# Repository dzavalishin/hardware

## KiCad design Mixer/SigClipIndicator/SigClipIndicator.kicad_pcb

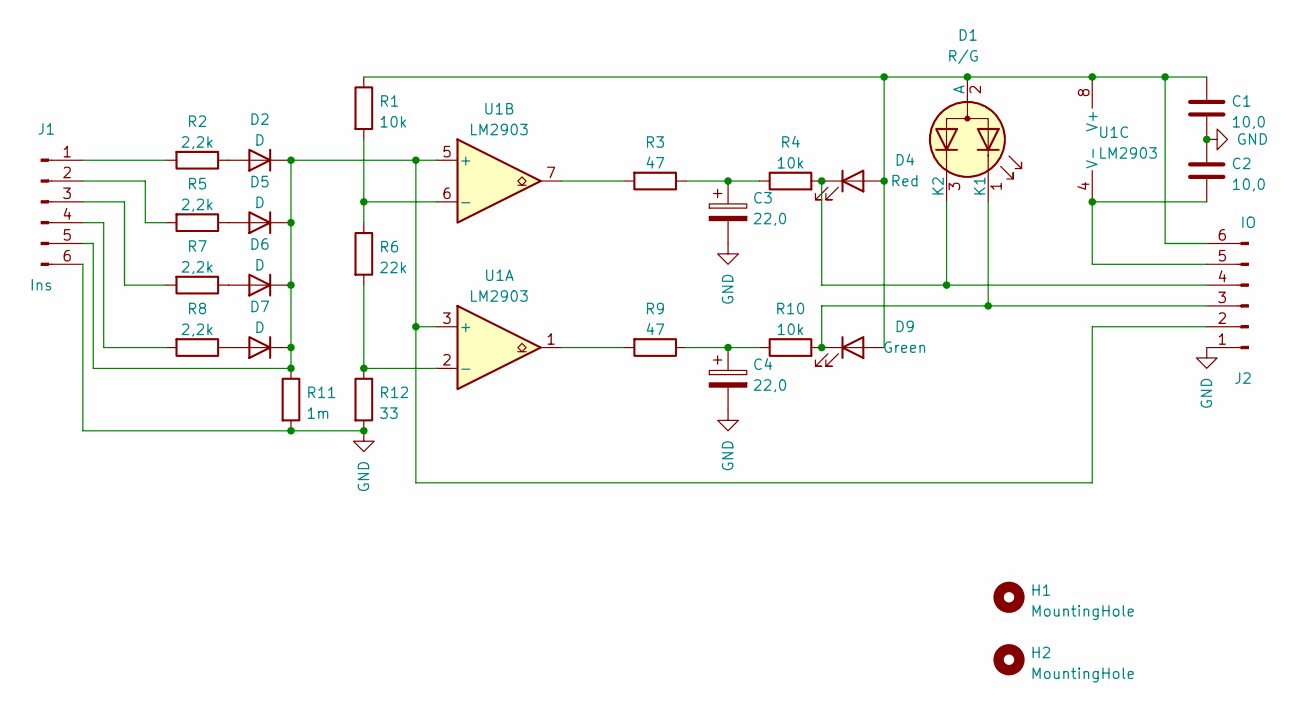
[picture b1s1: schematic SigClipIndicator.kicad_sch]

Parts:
C1, C2: 10,0; C_0805_2012Metric_Pad1.18x1.45mm_HandSolder
C3, C4: 22,0; C_0805_2012Metric_Pad1.18x1.45mm_HandSolder
D1: R/G; LED_D3.0mm-3
D2, D5, D6, D7: D; D_MiniMELF_Handsoldering
D4: Red; LED_D3.0mm
D9: Green; LED_D3.0mm
H1, H2: MountingHole; MountingHole_2.2mm_M2
J1: Ins; PinHeader_1x06_P2.54mm_Vertical
J2: IO; PinHeader_1x06_P2.54mm_Vertical
R1, R4, R10: 10k; R_1206_3216Metric_Pad1.30x1.75mm_HandSolder
R2, R5, R7, R8: 2,2k; R_1206_3216Metric_Pad1.30x1.75mm_HandSolder
R3, R9: 47; R_1206_3216Metric_Pad1.30x1.75mm_HandSolder
R6: 22k; R_1206_3216Metric_Pad1.30x1.75mm_HandSolder
R11: 1m; R_1206_3216Metric_Pad1.30x1.75mm_HandSolder
R12: 33; R_1206_3216Metric_Pad1.30x1.75mm_HandSolder
U1: LM2903; SOIC-8_3.9x4.9mm_P1.27mm

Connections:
GND: C1.1, C2.2, C3.2, C4.2, J1.6, J2.1, R11.2, R12.2
unnamed: C1.2, D1.2 (A), D4.2 (A), D9.2 (A), J2.6, R1.1, U1.8 (V+)
unnamed: C2.1, J2.5, U1.4 (V-)
unnamed: C3.1, R3.1, R4.1
unnamed: C4.1, R9.1, R10.1
unnamed: D1.1 (K1), D9.1 (K), J2.3, R10.2
unnamed: D1.3 (K2), D4.1 (K), J2.4, R4.2
unnamed: D2.1 (K), D5.1 (K), D6.1 (K), D7.1 (K), J1.5, J2.2, R11.1, U1.3 (+), U1.5 (+)
unnamed: D2.2 (A), R2.1
unnamed: D5.2 (A), R5.1
unnamed: D6.2 (A), R7.1
unnamed: D7.2 (A), R8.1
unnamed: J1.1, R2.2
unnamed: J1.2, R5.2
unnamed: J1.3, R7.2
unnamed: J1.4, R8.2
unnamed: R1.2, R6.1, U1.6 (-)
unnamed: R3.2, U1.7
unnamed: R9.2, U1.1
unnamed: R6.2, R12.1, U1.2 (-)

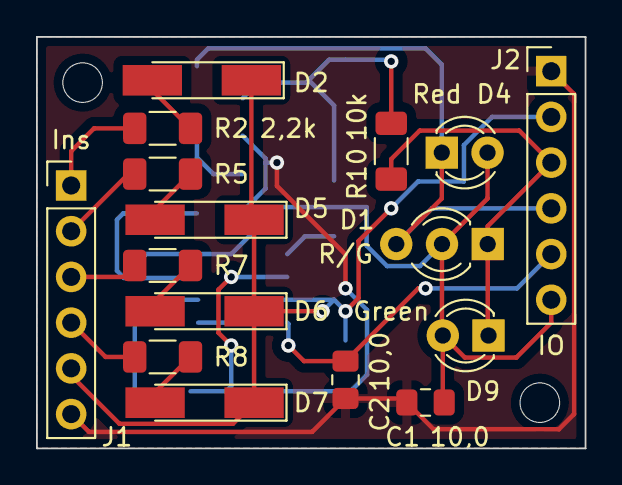
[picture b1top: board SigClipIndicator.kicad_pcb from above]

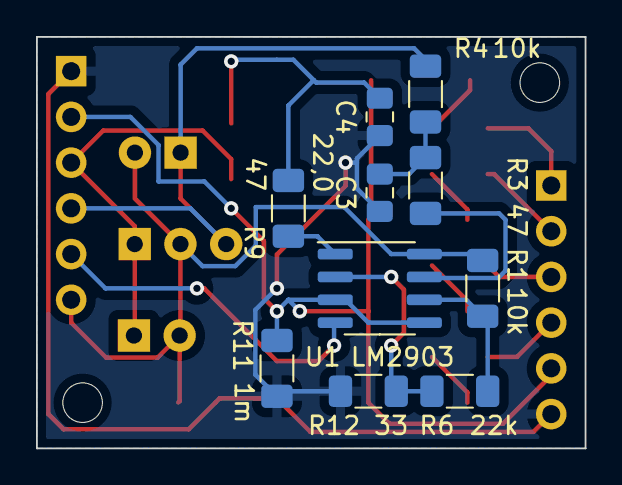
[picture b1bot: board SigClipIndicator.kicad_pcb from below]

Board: 2 copper layers, 30.5 x 22.9 mm, 28 parts (10 on the bottom side), 20 nets.

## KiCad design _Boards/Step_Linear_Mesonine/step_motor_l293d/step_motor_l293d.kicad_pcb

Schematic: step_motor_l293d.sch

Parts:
C1, C3, C5: 0,1; C_1206_HandSoldering
C4, C8: 47,0; CP_Elec_6.3x5.3
C6, C7: 1,0; C_0805_HandSoldering
C9, C10: 0,33; C_0805_HandSoldering
C11: 100,0; CP_Elec_6.3x5.7
D1: A; LED_1206_HandSoldering
D2: B; LED_1206_HandSoldering
D3: Over; LED_1206_HandSoldering
D4: D; LED_1206_HandSoldering
D5: C; LED_1206_HandSoldering
J1: Motor; Pin_Header_Straight_1x04_Pitch2.54mm
J2: +12; TerminalBlock_bornier-2_P5.08mm
J3: In; Pin_Header_Straight_1x06_Pitch2.54mm
J4: Pwr; Pin_Header_Straight_1x06_Pitch2.54mm
Q1: MMBT3904; SOT-23
R1: 0,2 2W 1%; R_2512_HandSoldering
R2: 200 1%; R_1206_HandSoldering
R3: 1,5m; R_1206_HandSoldering
R4, R5, R7, R10, R11, R12: 10k; R_1206_HandSoldering
R6: 9,1k; R_1206_HandSoldering
R8, R9, R14, R15, R16: 560; R_1206_HandSoldering
R13: 2k 1%; R_1206_HandSoldering
RV1: 1m; Potentiometer_Trimmer_Bourns_3296W
RV2: 1k; Potentiometer_Triwood_RM-065
U1: TL082; DIP-8_W7.62mm
U2: L293D; DIP-16_W7.62mm
U3: L78L05; TO-92_Inline_Narrow_Oval

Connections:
+5V: C3.1, C10.1, C11.1, J4.2, U2.16, U3.1
+12V: C1.1, C8.1, C9.1, J4.1, R1.1, R2.1, R6.2, U1.8, U3.3; also elsewhere on the board
/Buck/Power_In: J2.2; also elsewhere on the board
/MA: J3.1, U2.2
/MB: J3.3, U2.7
/MC: J3.4, U2.10
/MD: J3.2, U2.15
/MPower: C4.1, C5.1, R1.2, R4.1, U2.8
/Overload: J4.4, R3.1, R14.2, U1.7
/Run: J3.5, U2.1, U2.9
/Sense: C6.1, J4.3, Q1.2, R7.2, R13.1
GND: C1.2, C3.2, C4.2, C5.2, C6.2, C7.2, C8.2, C9.2, C10.2, C11.2, D1.1, D2.1, D3.1, D4.1, D5.1, J2.1, J3.6, J4.6, R11.2, R12.2, R13.2, RV2.3, U1.4, U2.4, U2.5, U2.12, U2.13, U3.2; also elsewhere on the board
unnamed: C7.1, R10.2, RV2.2
unnamed: D1.2, R8.1
unnamed: D2.2, R9.1
unnamed: D3.2, R14.1
unnamed: D4.2, R15.2
unnamed: D5.2, R16.2
unnamed: J1.1, R15.1, U2.14
unnamed: J1.2, R16.1, U2.11
unnamed: J1.3, R9.2, U2.6
unnamed: J1.4, R8.2, U2.3
unnamed: Q1.1, U1.1
unnamed: Q1.3, R2.2, R5.1
unnamed: R3.2, RV1.3
unnamed: R6.1, RV2.1
unnamed: R7.1, RV1.1, RV1.2, U1.5
unnamed: R10.1, U1.6
unnamed: R4.2, R11.1, U1.2
unnamed: R5.2, R12.1, U1.3

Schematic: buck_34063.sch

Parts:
C2, C12, C14: 0,1; C_1206_HandSoldering
C13, C16: 100,0; CP_Elec_6.3x5.7
C15: 220,0; CP_Elec_6.3x5.7
C17: 390; C_1206_HandSoldering
D6, D7: SS34; D_SMB-SMC_Universal_Handsoldering
L1: 100uH; Inductor_Taiyo-Yuden_NR-40xx_HandSoldering
L2: 47uH; Inductor_Taiyo-Yuden_NR-40xx_HandSoldering
R17: 1,5 1W; R_2512_HandSoldering
R18: 11k; R_1206_HandSoldering
R19: 1,3k; R_1206_HandSoldering
U4: MC34063; SOIC-8_3.9x4.9mm_Pitch1.27mm

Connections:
+12V: C16.1, L2.2, R18.2; also elsewhere on the board
/Buck/Power_In: C12.2, D6.2; also elsewhere on the board
GND: C2.1, C12.1, C13.2, C14.2, C15.2, C16.2, C17.2, D7.2, R19.2, U4.4; also elsewhere on the board
unnamed: C2.2, R17.2, U4.1, U4.7, U4.8
unnamed: C13.1, D6.1, R17.1, U4.6
unnamed: C14.1, C15.1, L1.2, L2.1
unnamed: C17.1, U4.3
unnamed: D7.1, L1.1, U4.2
unnamed: R18.1, R19.1, U4.5

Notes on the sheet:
12v out, 1.25v sense level

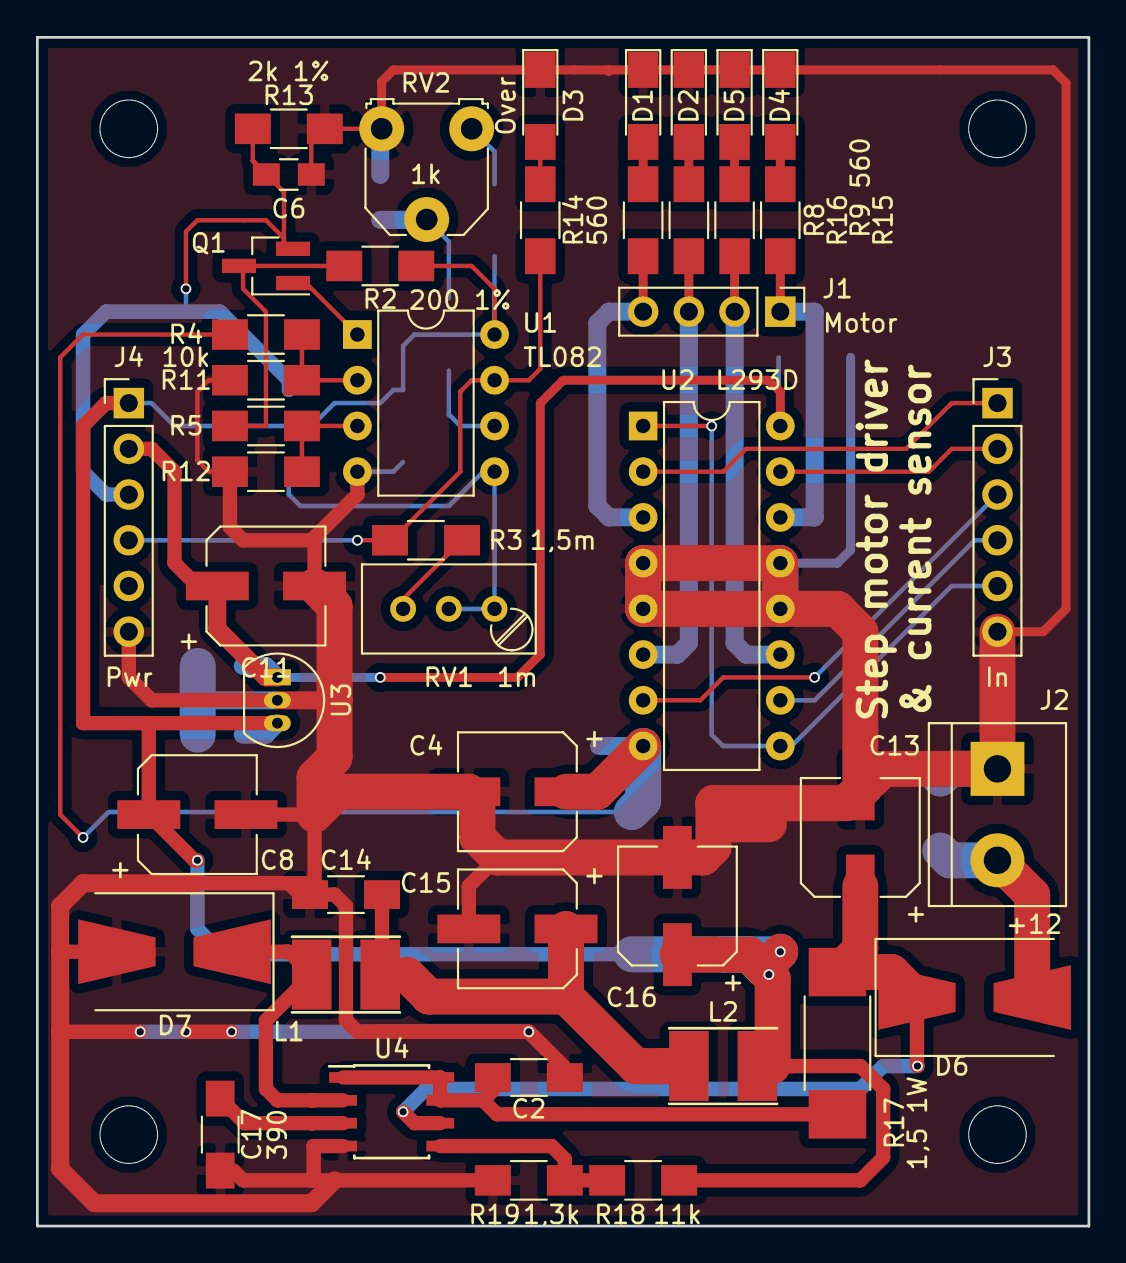
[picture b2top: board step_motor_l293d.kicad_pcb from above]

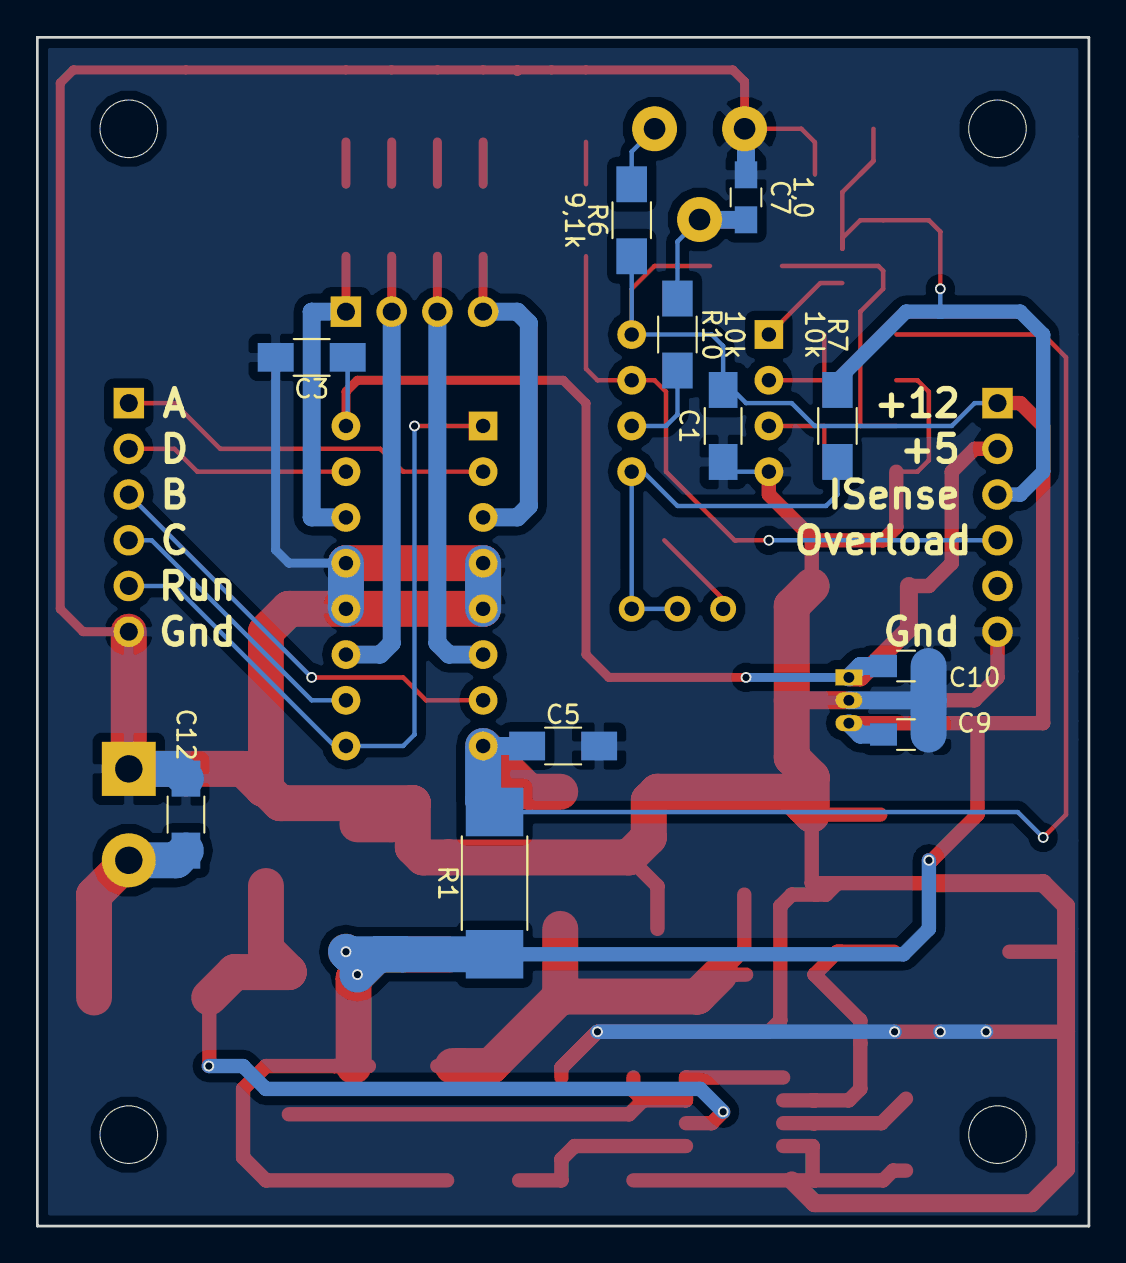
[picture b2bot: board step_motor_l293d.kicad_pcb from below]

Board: 2 copper layers, 58.4 x 66.0 mm, 60 parts (11 on the bottom side), 36 nets.

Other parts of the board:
Hole: MountingHole_3.2mm_M3
Hole#2, Hole#3, Hole#4: MountingHole_3.2mm_M3

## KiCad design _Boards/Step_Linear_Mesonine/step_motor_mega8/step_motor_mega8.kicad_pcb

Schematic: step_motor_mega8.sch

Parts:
C1, C2, C3: 0,1; C_1206_HandSoldering
C4, C5: 18; C_1206_HandSoldering
D1: Err; LED_1206_HandSoldering
D2: Tx; LED_1206_HandSoldering
D3: Run; LED_1206_HandSoldering
D4: 5v6; D_1206
J1: ISP; Socket_Strip_Straight_2x05_Pitch2.54mm
J3: In; Pin_Header_Straight_1x06_Pitch2.54mm
J4: Pwr; Pin_Header_Straight_1x06_Pitch2.54mm
J5: RS485; TerminalBlock_bornier-2_P5.08mm
J6: Open/~Close; TerminalBlock_bornier-2_P5.08mm
R1: 10k; R_1206_HandSoldering
R2, R3: 47; R_1206_HandSoldering
R4, R5, R6, R8: 560; R_1206_HandSoldering
R7, R9: 1k; R_1206_HandSoldering
U1: ATMEGA8-16PU; DIP-28_W7.62mm
U2: MAX485E; SOIC-8_3.9x4.9mm_Pitch1.27mm
U3: PC817; SOP-4_4.4x2.8mm_Pitch1.27mm
Y1: 8MHz; Crystal_HC49-4H_Vertical

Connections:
+5V: C1.2, C3.2, J4.2, R1.1, R9.1, U1.7, U1.20, U2.8 (VCC); also elsewhere on the board
/Di0: R9.2, U1.14, U3.4
/MA: J3.1, U1.27
/MB: J3.3, U1.25
/MC: J3.4, U1.24
/MD: J3.2, U1.26
/Overload: J4.4, U1.11
/Run: J3.5, R6.2, U1.23
/S1: U1.4; also elsewhere on the board
/S2: U1.5; also elsewhere on the board
GND: C1.1, C2.1, C3.1, C4.1, C5.1, D1.1, D2.1, D3.1, J1.4, J1.6, J1.8, J1.10, J3.6, J4.6, U1.8, U1.22, U2.5 (GND), U3.3; also elsewhere on the board
unnamed: C2.2, J1.5, R1.2, U1.1
unnamed: C4.2, U1.9, Y1.1
unnamed: C5.2, U1.10, Y1.2
unnamed: D1.2, R4.1
unnamed: D2.2, R5.1
unnamed: D3.2, R6.1
unnamed: D4.1, R7.1, R8.1
unnamed: D4.2, J6.1, U3.2
unnamed: J1.1, U1.17
unnamed: J1.7, U1.19
unnamed: J1.9, U1.18
unnamed: J5.1, R2.1
unnamed: J5.2, R3.1
unnamed: J6.2, R7.2
unnamed: R2.2, U2.7 (B)
unnamed: R3.2, U2.6 (A)
unnamed: R4.2, U1.28
unnamed: R5.2, U1.6, U2.2 (~RE), U2.3 (DE)
unnamed: R8.2, U3.1
unnamed: U1.2, U2.1 (RO)
unnamed: U1.3, U2.4 (DI)

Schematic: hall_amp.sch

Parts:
C10: 0,1; C_1206_HandSoldering
C11: 1,0; C_0805_HandSoldering
D6: S1; LED_1206_HandSoldering
D7: S2; LED_1206_HandSoldering
J2: Hall; Pin_Header_Angled_2x03_Pitch2.54mm
R13, R20, R22, R23, R27, R28: 1k; R_1206_HandSoldering
R21, R26: 220k; R_1206_HandSoldering
R24, R25: 560; R_1206_HandSoldering
RV3: 1k; Potentiometer_Triwood_RM-065
U6: LM2904; SOIC-8_3.9x4.9mm_Pitch1.27mm

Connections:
+5V: C10.1, J2.5, J2.6, R13.2, U6.8; also elsewhere on the board
/S1: R21.1, R24.2, U6.1; also elsewhere on the board
/S2: R25.2, R26.1, U6.7; also elsewhere on the board
GND: C10.2, C11.2, D6.1, D7.1, J2.3, J2.4, R20.1, U6.4; also elsewhere on the board
unnamed: C11.1, R23.2, R28.2, RV3.2
unnamed: D6.2, R24.1
unnamed: D7.2, R25.1
unnamed: J2.1, R22.2
unnamed: J2.2, R27.2
unnamed: R13.1, RV3.1
unnamed: R20.2, RV3.3
unnamed: R21.2, R22.1, U6.3
unnamed: R23.1, U6.2
unnamed: R26.2, R27.1, U6.5
unnamed: R28.1, U6.6

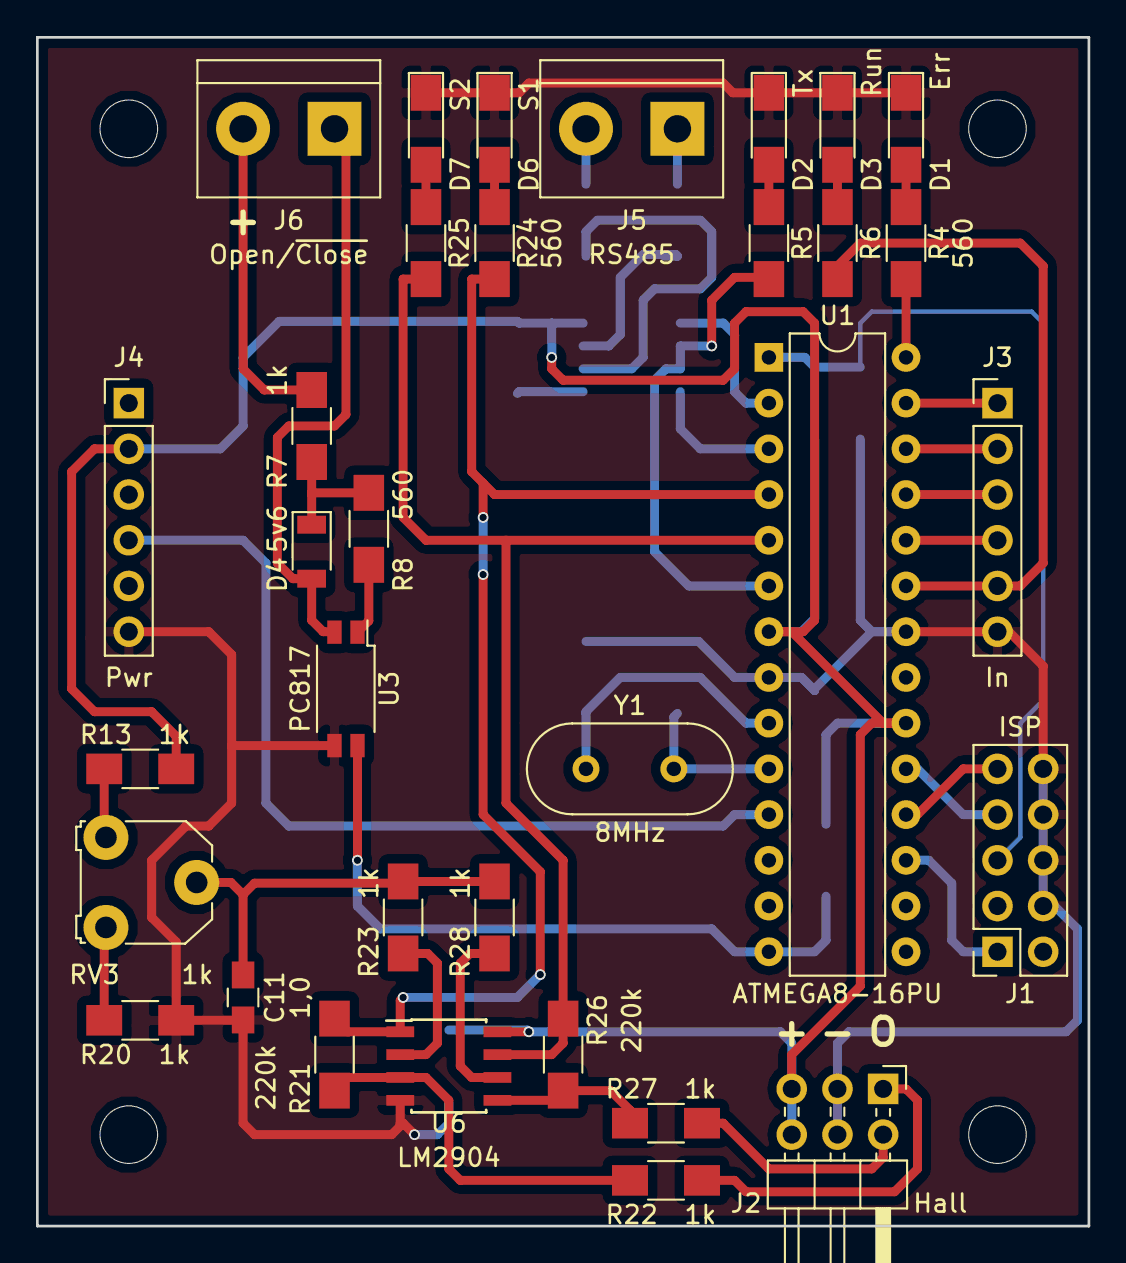
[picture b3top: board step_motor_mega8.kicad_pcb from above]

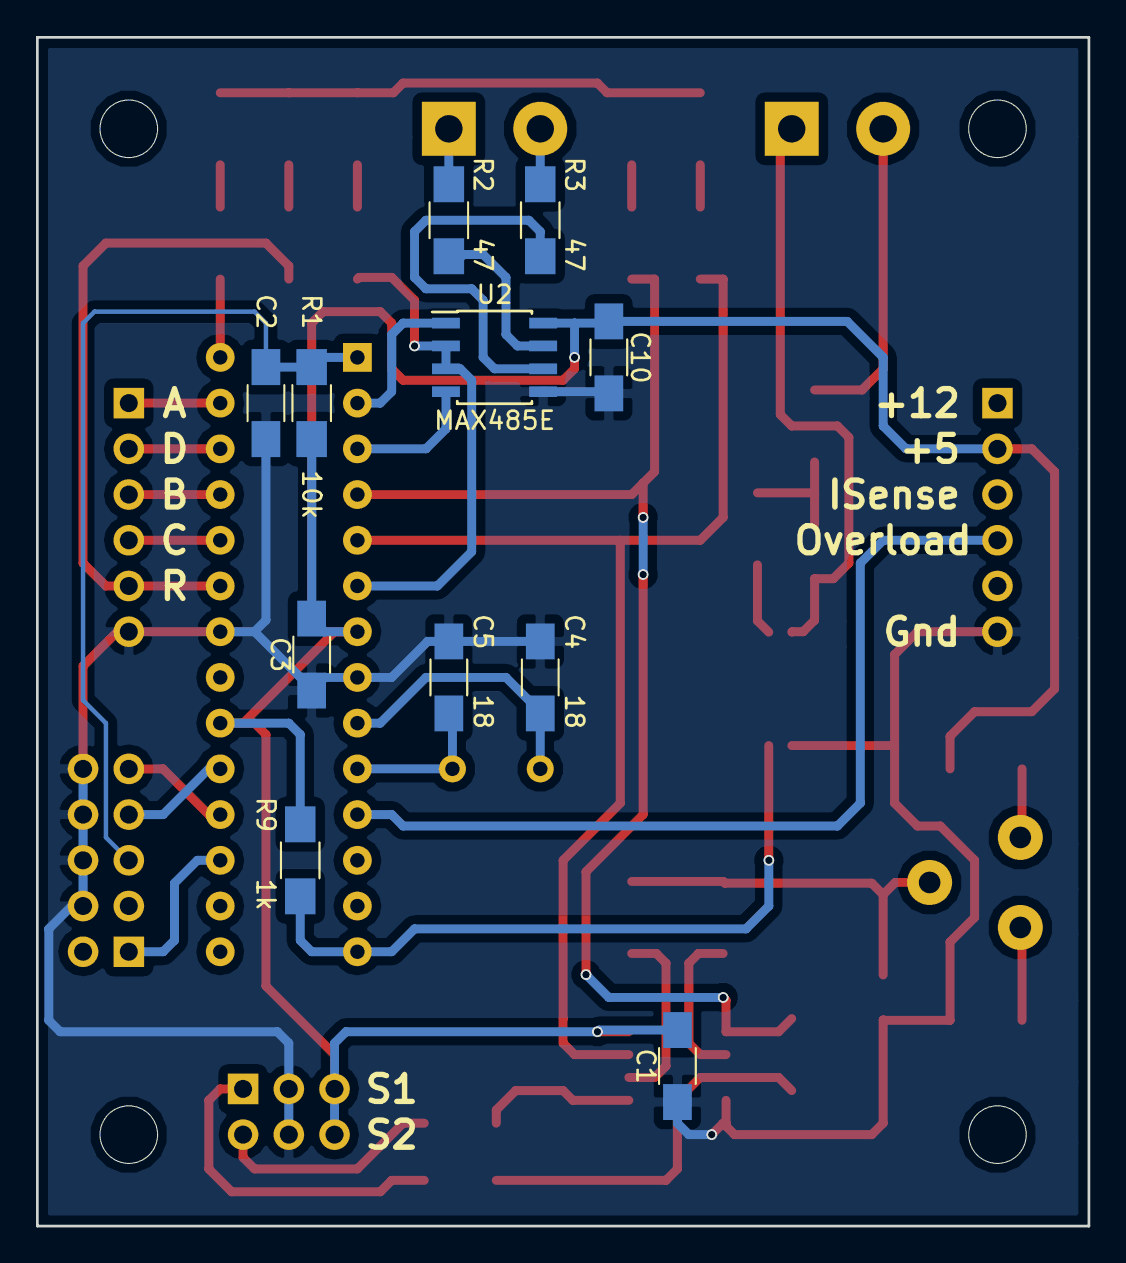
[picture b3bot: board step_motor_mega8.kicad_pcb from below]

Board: 2 copper layers, 58.4 x 66.0 mm, 48 parts (11 on the bottom side), 43 nets.

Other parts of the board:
Hole: MountingHole_3.2mm_M3
Hole#2, Hole#3, Hole#4: MountingHole_3.2mm_M3

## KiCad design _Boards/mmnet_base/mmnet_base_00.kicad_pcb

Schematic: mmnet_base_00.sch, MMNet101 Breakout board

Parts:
C1, C2, C4, C6: 0,1; C_1206_HandSoldering
C3: 100,0; SMD-2512_Pol
C5: 10,0; SMD-2512_Pol
D1: D; D_MELF_Handsoldering
D2: Pwr; LED_D3.0mm
D3: Tx0; LED_D3.0mm
D4: Tx1; LED_D3.0mm
D5: Fail; LED_D3.0mm
D6: IO; LED_D3.0mm
F1: 0,1A; SMD-1206_Pol
J1: 24V; TerminalBlock_Pheonix_MPT-2.54mm_2pol
J2: RS485; TerminalBlock_Pheonix_MPT-2.54mm_2pol
J3: Ext_IO_0; TerminalBlock_Pheonix_MPT-2.54mm_3pol
J4: Ext_IO_1; TerminalBlock_Pheonix_MPT-2.54mm_5pol
J5: Ai0-1; TerminalBlock_Pheonix_MPT-2.54mm_3pol
J6: Ai2-3; TerminalBlock_Pheonix_MPT-2.54mm_3pol
J7: 1Wire; TerminalBlock_Pheonix_MPT-2.54mm_6pol
P1: VR+In; Socket_Strip_Straight_1x01
P2: VR-In; Socket_Strip_Straight_1x01
P3: Bus; Socket_Strip_Straight_2x05
P4: VR+Out; Socket_Strip_Straight_1x01
P5: VR-Out; Socket_Strip_Straight_1x01
P6: MMNet_L; Socket_Strip_Straight_1x20
P7: MMNet_R; Socket_Strip_Straight_1x20
P10: Extension; Socket_Strip_Straight_2x08
P11: JTAG/AnalogExt; Socket_Strip_Straight_2x05
R1, R2, R3, R4, R5, R6, R11: 4,7k; R_1206_HandSoldering
R7, R8, R9, R10, R12: 5,6k; R_1206_HandSoldering
R13, R14: 3k 1%; R_Axial_DIN0207_L6.3mm_D2.5mm_P10.16mm_Horizontal
R15, R16: 27k 1%; R_Axial_DIN0204_L3.6mm_D1.6mm_P2.54mm_Vertical
R17, R18, R19, R20: 100; R_1206_HandSoldering
R21, R22, R23, R24: 10k; R_1206_HandSoldering
U1: SP3485CN; SOIC-8_3.9x4.9mm_Pitch1.27mm
U2: DS2401; TO-92_Rugged
U3: DS18B20; TO-92_Rugged

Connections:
+5V: C1.1, C2.1, C3.1, D5.2, D6.2, F1.2, P3.6, P4.1, P6.19, P10.8, P11.4, R1.2, R2.2, R3.2, R4.2, R5.2, R6.2, R7.2, R11.1, R21.2, R22.2, R23.2, R24.2, U1.8 (VCC), U3.3 (VDD)
/1Wire: P7.18, R11.2, U2.2 (DQ), U3.2 (DQ)
/1Wire_B0: P6.13, R3.1, R17.2
/1Wire_B1: P6.14, R4.1, R18.2
/1Wire_B2: P6.15, R5.1, R19.2
/1Wire_B3: P6.16, R6.1, R20.2
/ADC0: J5.3, P7.10
/ADC1: J5.1, P7.11
/ADC2: P7.12, R13.1, R15.2
/ADC3: P7.13, R14.1, R16.2
/ADC4/TCK: P7.14, P11.1, R21.1
/ADC5/TMS: P7.15, P11.5, R22.1
/ADC6/TDO: P7.16, P11.3, R23.1
/ADC7/TDI: P7.17, P11.9, R24.1
/ARef: C4.2, P7.9
/I2C_SCL: P3.8, P6.9, P10.5, R1.1
/I2C_SDA: P3.4, P6.10, P10.7, R2.1
/LED_Fail: P7.4, R10.2
/LED_Io: P7.19, R12.2
/RxD0: P7.8, P10.16
/RxD1: P6.11, U1.1 (RO)
/SPI_MISO: P3.7, P6.4
/SPI_MOSI: P3.5, P6.3
/SPI_SCK: P3.3, P6.2
/TxD0: P7.7, P10.14
/TxD1: P6.12, U1.4 (DI)
/TxE0: P6.7, R8.2
/TxE1: P6.8, R9.2, U1.2 (~RE~), U1.3 (DE)
/~Reset: P7.20, P11.6
/~SS0: P3.1, P6.1
/~SS1: P3.9, P6.5
GND: C1.2, C2.2, C3.2, C4.1, C5.2, C6.1, D2.1, D3.1, D4.1, J1.2, J3.2, J4.1, J5.2, J6.2, J7.6, P2.1, P3.2, P3.10, P5.1, P6.20, P10.6, P11.2, P11.10, R13.2, R14.2, U1.5 (GND), U2.1 (GND), U3.1 (GND)
unnamed: C5.1, C6.2, F1.1, J7.1
unnamed: D1.1, P1.1
unnamed: D1.2, J1.1
unnamed: D2.2, R7.1
unnamed: D3.2, R8.1
unnamed: D4.2, R9.1
unnamed: D5.1, R10.1
unnamed: D6.1, R12.1
unnamed: J2.1, U1.6 (A)
unnamed: J2.2, U1.7 (B)
unnamed: J3.1, P10.3
unnamed: J3.3, P10.1
unnamed: J4.2, P10.15
unnamed: J4.3, P10.13
unnamed: J4.4, P10.11
unnamed: J4.5, P10.9
unnamed: J6.1, R16.1
unnamed: J6.3, R15.1
unnamed: J7.2, R17.1
unnamed: J7.3, R18.1
unnamed: J7.4, R19.1
unnamed: J7.5, R20.1
unnamed: P7.1, P10.2
unnamed: P7.2, P10.4
unnamed: P7.5, P10.10
unnamed: P7.6, P10.12

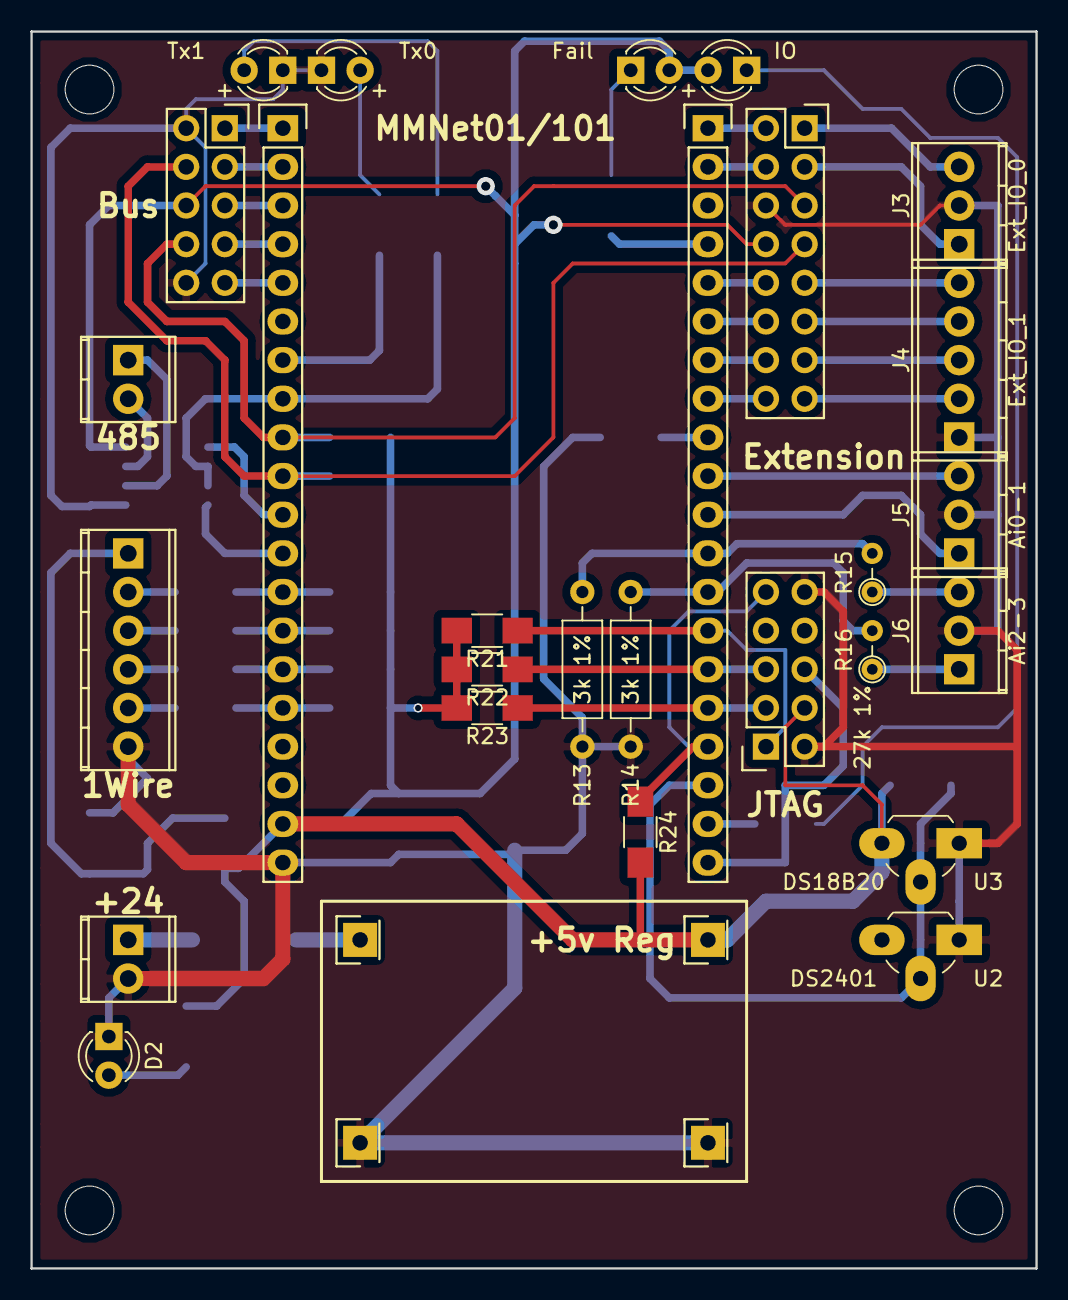
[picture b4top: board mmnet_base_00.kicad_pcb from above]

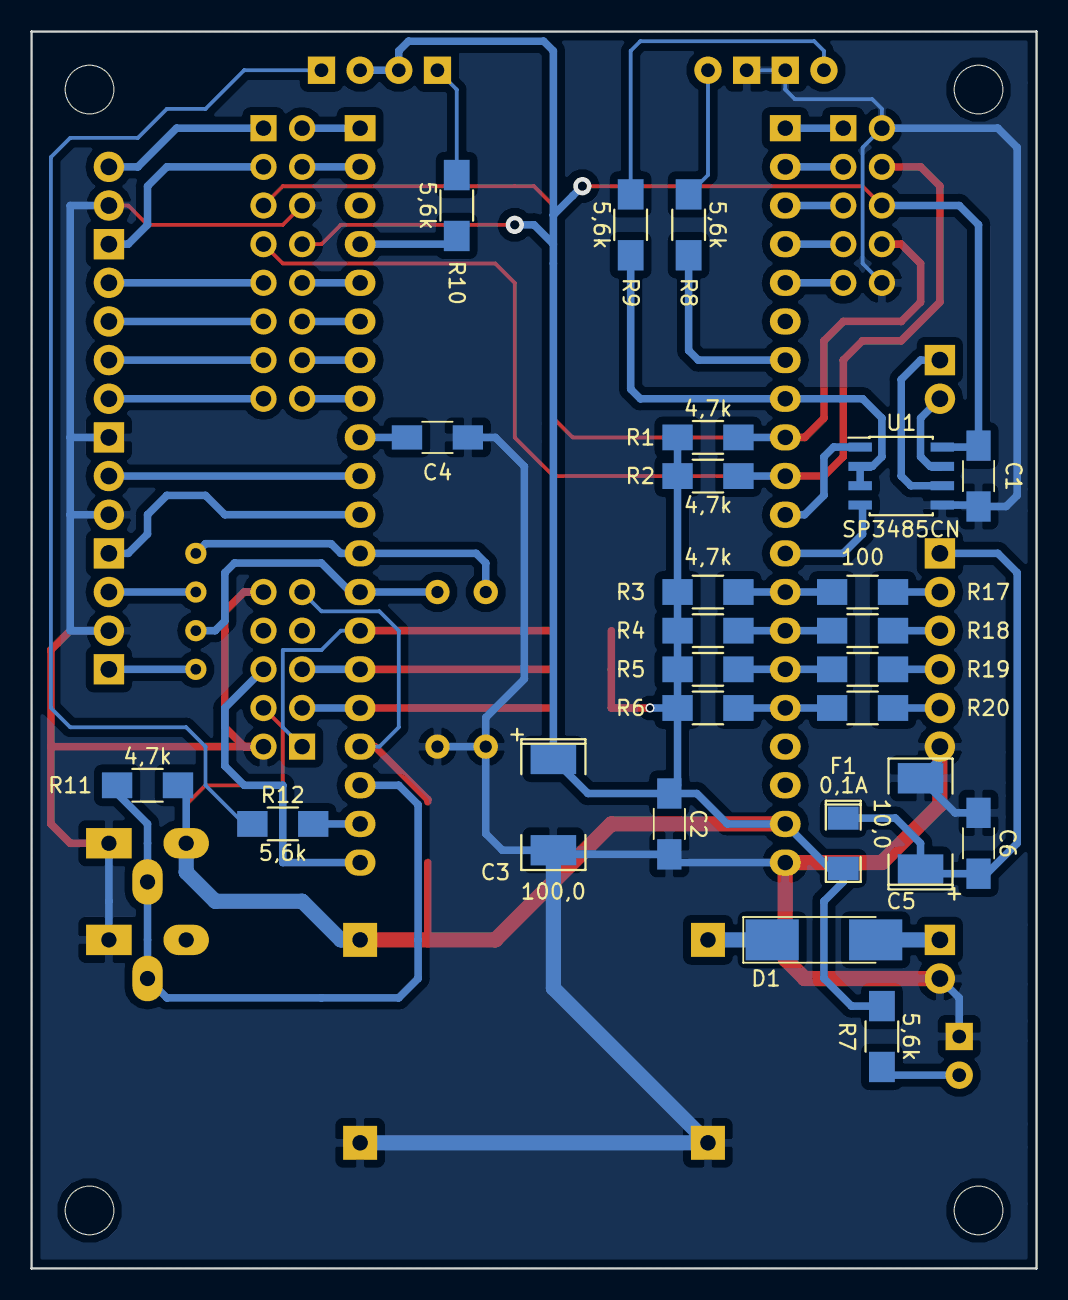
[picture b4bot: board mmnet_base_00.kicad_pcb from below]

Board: 2 copper layers, 66.0 x 81.3 mm, 60 parts (25 on the bottom side), 58 nets.

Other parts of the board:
hole: MountingHole_3.2mm_M3
hole#2, hole#3, hole#4: MountingHole_3.2mm_M3

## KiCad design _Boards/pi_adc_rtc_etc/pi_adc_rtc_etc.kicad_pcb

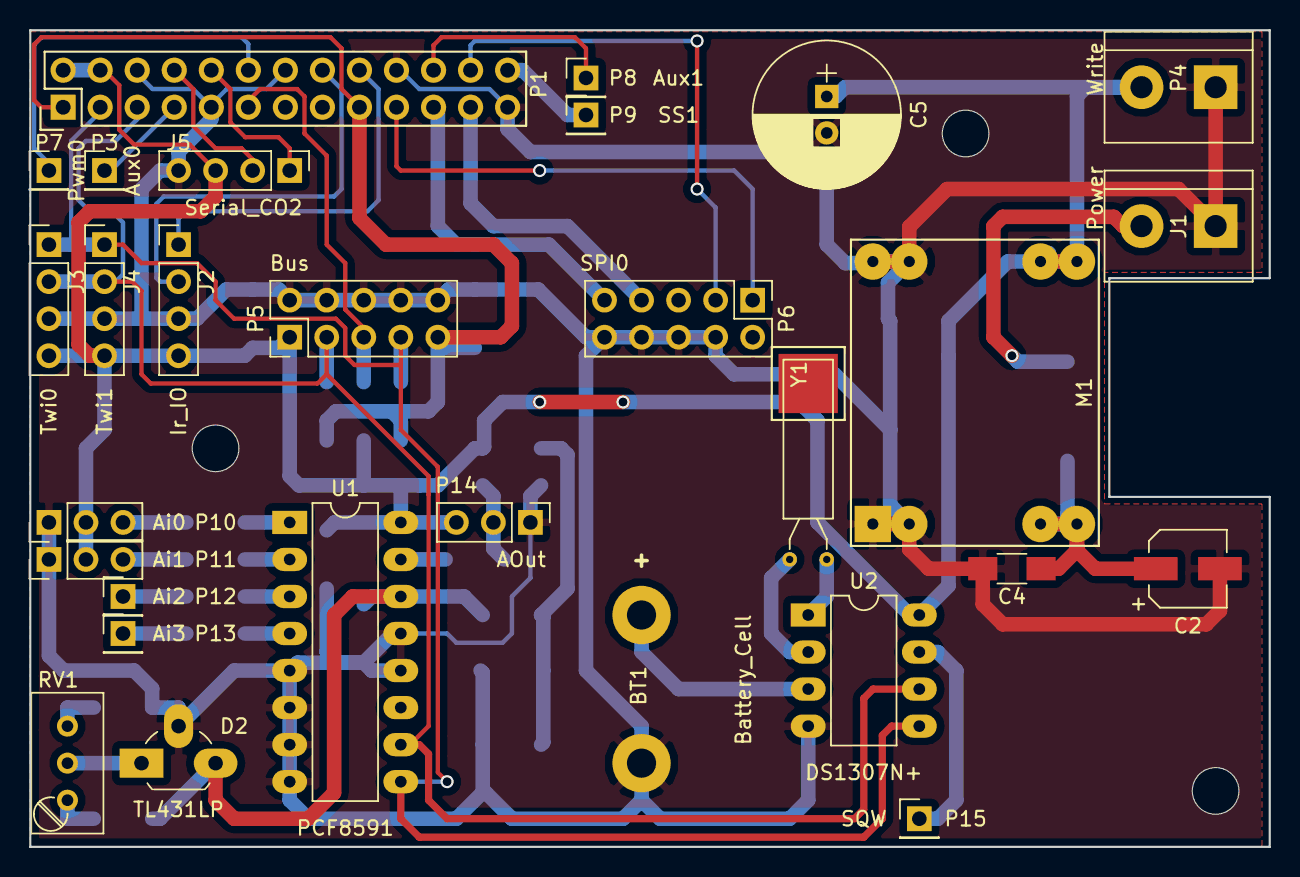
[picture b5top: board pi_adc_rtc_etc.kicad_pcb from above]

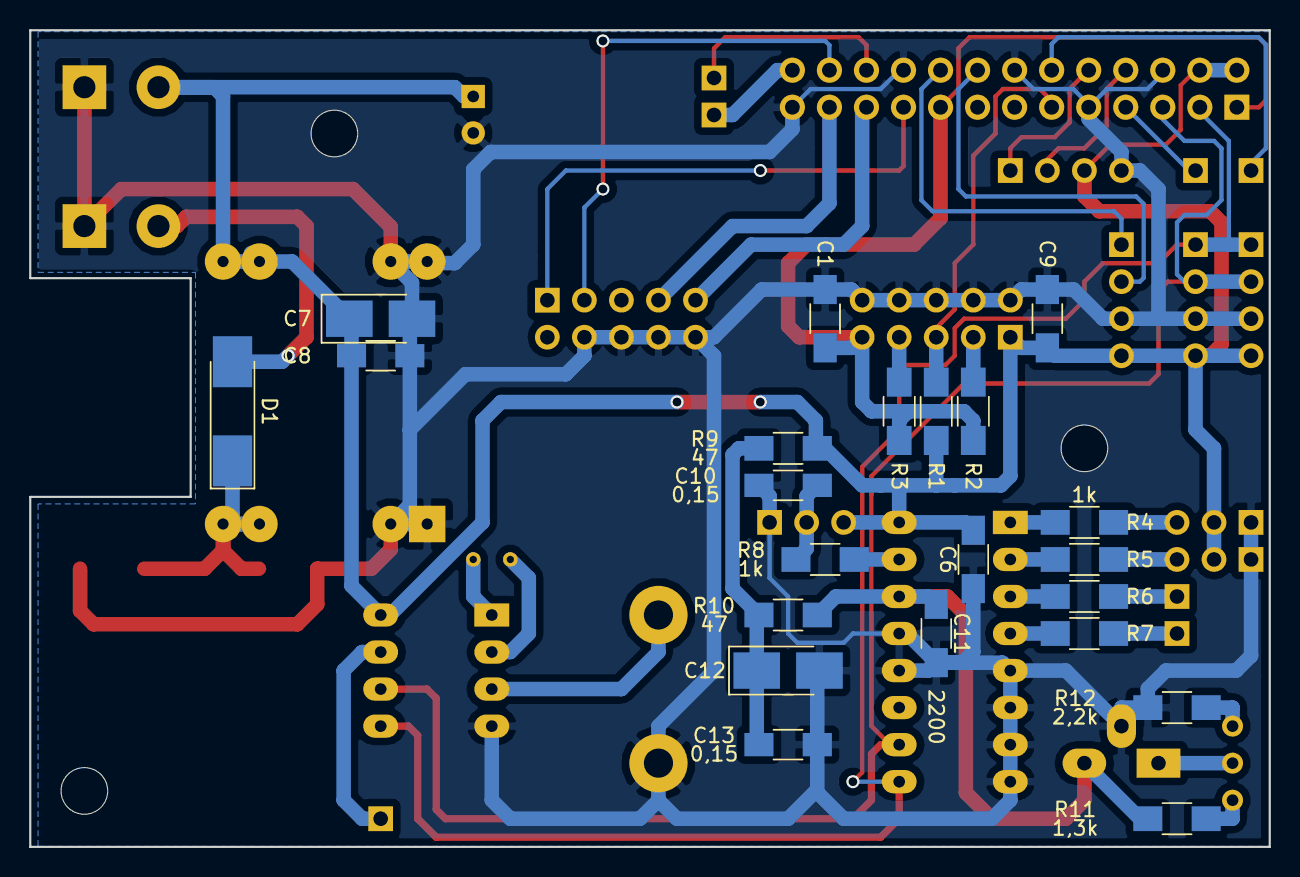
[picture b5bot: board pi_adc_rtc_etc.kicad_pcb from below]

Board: 2 copper layers, 85.0 x 56.0 mm, 55 parts (22 on the bottom side), 39 nets.

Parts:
BT1: Battery_Cell; WireConnection_2.00mmDrill
C1, C6, C9: 0,1; C_1206_HandSoldering
C2: CP; CP_Elec_5x5.8
C4: C; C_1206_HandSoldering
C5: 100,0; CP_Radial_D10.0mm_P2.50mm
C7: 100,0; CP_Tantalum_Case-B_EIA-3528-21_Hand
C8, C10, C13: 0,15; C_1206_HandSoldering
C11: 2200; C_1206_HandSoldering
C12: 220,0; CP_Tantalum_Case-B_EIA-3528-21_Hand
D1: D; D_MELF_Handsoldering
D2: TL431LP; TO-92_Rugged
J1: Power; TerminalBlock_bornier-2_P5.08mm
J2: Ir_IO; Pin_Header_Straight_1x04_Pitch2.54mm
J3: Twi0; Pin_Header_Straight_1x04_Pitch2.54mm
J4: Twi1; Pin_Header_Straight_1x04_Pitch2.54mm
J5: Serial_CO2; Pin_Header_Straight_1x04_Pitch2.54mm
M1: dcdc5v
P1: CONN_13X2; Pin_Header_Straight_2x13
P3: Aux0; Pin_Header_Straight_1x01_Pitch2.54mm
P4: Write; TerminalBlock_bornier-2_P5.08mm
P5: Bus; Pin_Header_Straight_2x05_Pitch2.54mm
P6: SPI0; Pin_Header_Straight_2x05_Pitch2.54mm
P7: Pwm0; Pin_Header_Straight_1x01_Pitch2.54mm
P8: Aux1; Pin_Header_Straight_1x01_Pitch2.54mm
P9: SS1; Pin_Header_Straight_1x01_Pitch2.54mm
P10: Ai0; Pin_Header_Straight_1x03_Pitch2.54mm
P11: Ai1; Pin_Header_Straight_1x03_Pitch2.54mm
P12: Ai2; Pin_Header_Straight_1x01_Pitch2.54mm
P13: Ai3; Pin_Header_Straight_1x01_Pitch2.54mm
P14: AOut; Pin_Header_Straight_1x03_Pitch2.54mm
P15: SQW; Pin_Header_Straight_1x01_Pitch2.54mm
R1, R2, R3: 4,7k; R_1206_HandSoldering
R4, R5, R6, R7, R8: 1k; R_1206_HandSoldering
R9, R10: 47; R_1206_HandSoldering
R11: 1,3k; R_1206_HandSoldering
R12: 2,2k; R_1206_HandSoldering
RV1: 1k; Potentiometer_Trimmer_Bourns_3296W
U1: PCF8591; DIP-16_W7.62mm_LongPads
U2: DS1307N+; DIP-8_W7.62mm_LongPads
Y1: Crystal; Crystal_AT310_d3.0mm_l10.0mm_Horizontal
hole: MountingHole_3.2mm_M3
hole#2, hole#3: MountingHole_3.2mm_M3
xtal solder: 1Pin

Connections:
+3V3: C1.1, P1.1, P1.17, P5.9, R2.2, R3.2
+5V: C5.1, C6.2, C7.1, C8.2, C9.1, J2.4, J3.4, J4.4, J5.3, M1.3, P1.2, P1.4, P4.2, P5.1, P10.2, P11.2, P14.3, R1.2, R9.2, U1.16, U2.8
/1W: P1.11, P5.5, R1.1
/AUX0: P1.7, P3.1
/AUX1: P1.22, P8.1
/Ir_RX: J2.2, P1.16
/Ir_TX: J2.1, P1.18
/MISO: P1.21, P6.9
/MOSI: P1.19, P6.1
/Pwm0: P1.12, P7.1
/RXD: J5.1, P1.10
/SCK: P1.23, P6.7
/SCL: J3.2, J4.2, P1.5, P5.3, R2.1, U1.10, U2.6
/SDA: J3.1, J4.1, P1.3, P5.7, R3.1, U1.9, U2.5
/SS0: P1.24, P6.3
/SS1: P1.26, P9.1
/TXD: J5.2, P1.8
GND: BT1.2, C1.2, C2.2, C4.2, C5.2, C6.1, C7.2, C8.1, C9.2, C10.2, C11.2, C12.2, C13.1, D2.2, J1.1, J2.3, J3.3, J4.3, J5.4, M1.1, M1.4, P1.6, P1.9, P1.14, P1.20, P1.25, P4.1, P5.2, P5.4, P5.6, P5.8, P5.10, P6.4, P6.6, P6.8, P6.10, P10.1, P11.1, P14.1, R12.1, U1.5, U1.6, U1.7, U1.8, U1.12, U1.13, U2.4
unnamed: BT1.1, U2.3
unnamed: C2.1, C4.1, D1.1, M1.2
unnamed: C10.1, P14.2, R8.1
unnamed: C11.1, D2.3, R10.1, R11.2, U1.14
unnamed: C12.1, C13.2, R9.1, R10.2
unnamed: D1.2, J1.2
unnamed: D2.1, RV1.2
unnamed: P10.3, R4.1
unnamed: P11.3, R5.1
unnamed: P12.1, R6.1
unnamed: P13.1, R7.1
unnamed: P15.1, U2.7
unnamed: R4.2, U1.1
unnamed: R5.2, U1.2
unnamed: R6.2, U1.3
unnamed: R7.2, U1.4
unnamed: R8.2, U1.15
unnamed: R11.1, RV1.1
unnamed: R12.2, RV1.3
unnamed: U2.1, Y1.1
unnamed: U2.2, Y1.2
